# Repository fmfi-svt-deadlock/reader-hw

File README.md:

# PROJECT MOVED

This repository is now hosted here: https://gitlab.com/project-deadlock/reader/rdr-hw-fluocerite-model0

# reader-hw
Schematic, PCB layout and box for the Reader

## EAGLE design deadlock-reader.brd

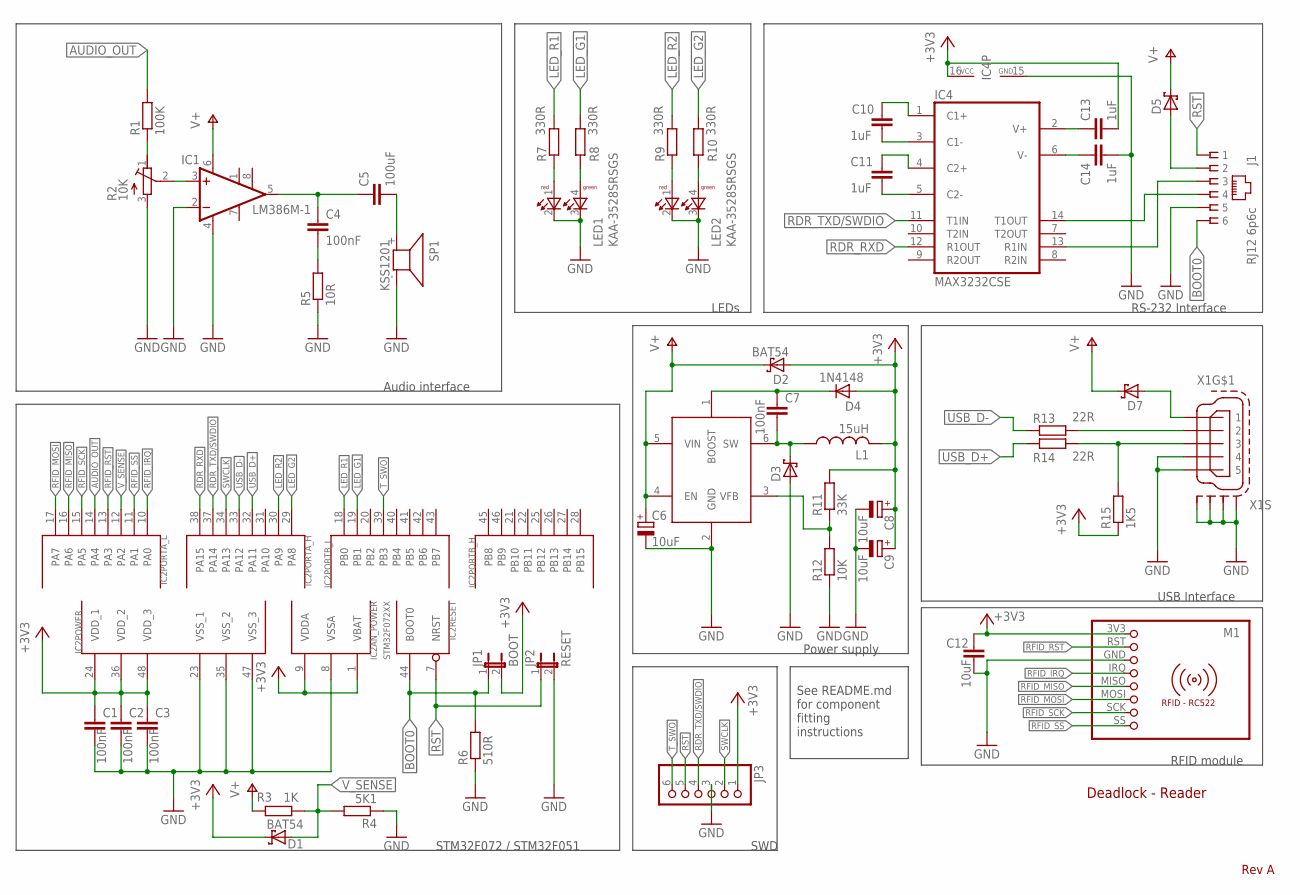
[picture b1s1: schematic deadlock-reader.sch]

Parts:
C1, C2, C3, C4, C7: 100nF; C0805
C5: 100uF; C1206
C6: 10uF; SMC_D
C8, C9: 10uF; A/3216-18R
C10, C11, C13, C14: 1uF; C0805
C12: 10uF; C0805
D1, D2: BAT54; SOT23
D3, D5, D7: BAT60J; SOD323_ST
D4: 1N4148; SOD323-W
IC1: LM386M-1; SO08
IC2: STM32F072XX; TQFP48
IC3: MCP16301/H; SOT23-6
IC4: MAX3232CSE; SO16
J1: RJ12 6p6c; RJ11-NO_SHIELD
JP1: BOOT; JP1
JP2: RESET; JP1
JP3: PINHD-1X6; 1X06
L1: 15uH; PIS2816
LED1, LED2: KAA-3528SRSGS
M1: RFID-RC522
R1: 100K; M0805
R2: 10K; RTRIM3314G
R3: 1K; R0805
R4: 5K1; R0805
R5: 10R; R0805
R6: 510R; R0805
R7, R8, R9, R10: 330R; R0805
R11: 33K; R0805
R12: 10K; R0805
R13, R14: 22R; R0805
R15: 1K5; R0805
SP1: KSS1201
X1: MINI-USB-SCHIELD-32005-301; 32005-301

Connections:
+3V3: C1.1, C2.1, C3.1, C8.+, C9.+, C12.1, C13.2, D1.3 (C), D2.1 (A), D4.A, IC2.1 (VBAT), IC2.9 (VDDA), IC2.24 (VDD_1), IC2.36 (VDD_2), IC2.48 (VDD_3), IC4.16 (VCC), JP1.2, JP3.1, L1.2, M1.3V3 (1), R11.2, R15.1
AUDIO_OUT: IC2.14 (PA4), R1.2
BOOT0: IC2.44 (BOOT0), J1.6, JP1.1, R6.2
GND: C1.2, C2.2, C3.2, C6.-, C8.-, C9.-, C12.2, C14.2, D3.A, IC1.2 (-IN), IC1.4 (GND), IC2.8 (VSSA), IC2.23 (VSS_1), IC2.35 (VSS_2), IC2.47 (VSS_3), IC3.2 (GND), IC4.15 (GND), J1.5, JP2.2, JP3.3, LED1.2 (C-RED), LED1.3 (C-GREEN), LED2.2 (C-RED), LED2.3 (C-GREEN), M1.GND (3), R2.3 (A), R4.1, R5.1, R6.1, R12.1, SP1.- (2), X1.4, X1.5, X1.M1 (S1), X1.M2 (S2), X1.M3 (S3), X1.M4 (S4)
LED_G1: IC2.19 (PB1), R8.2
LED_G2: IC2.29 (PA8), R10.2
LED_R1: IC2.18 (PB0), R7.2
LED_R2: IC2.30 (PA9), R9.2
unnamed: IC4.13 (R1IN), J1.3
unnamed: IC4.14 (T1OUT), J1.4
unnamed: C10.1, IC4.1 (C1+)
unnamed: C10.2, IC4.3 (C1-)
unnamed: C11.1, IC4.4 (C2+)
unnamed: C11.2, IC4.5 (C2-)
unnamed: C13.1, IC4.2 (V+)
unnamed: C14.1, IC4.6 (V-)
unnamed: D5.A, J1.2
unnamed: LED2.1 (A-RED), R9.1
unnamed: D7.A, X1.1
unnamed: R13.2, X1.2
unnamed: R14.2, R15.2, X1.3
unnamed: R1.1, R2.1 (E)
unnamed: IC1.3 (+IN), R2.2 (S)
unnamed: C4.1, C5.1, IC1.5 (OUT)
unnamed: C4.2, R5.2
unnamed: C5.2, SP1.+ (1)
unnamed: LED1.1 (A-RED), R7.1
unnamed: LED1.4 (A-GREEN), R8.1
unnamed: LED2.4 (A-GREEN), R10.1
unnamed: C7.2, D3.C, IC3.6 (SW), L1.1
unnamed: C7.1, D4.C, IC3.1 (BOOST)
unnamed: IC3.3 (VFB), R11.1, R12.2
RDR_RXD: IC2.38 (PA15), IC4.12 (R1OUT)
RDR_TXD/SWDIO: IC2.37 (PA14), IC4.11 (T1IN), JP3.4
RFID_IRQ: IC2.10 (PA0), M1.IRQ (4)
RFID_MISO: IC2.16 (PA6), M1.MISO (5)
RFID_MOSI: IC2.17 (PA7), M1.MOSI (6)
RFID_RST: IC2.13 (PA3), M1.RST (2)
RFID_SCK: IC2.15 (PA5), M1.SCK (7)
RFID_SS: IC2.11 (PA1), M1.SS (8)
RST: IC2.7 (NRST), J1.1, JP2.1, JP3.5
SWCLK: IC2.34 (PA13), JP3.2
T_SWO: IC2.39 (PB3), JP3.6
USB_D+: IC2.32 (PA11), R14.1
USB_D-: IC2.33 (PA12), R13.1
V+: C6.+, D2.3 (C), D5.C, D7.C, IC1.6 (VS), IC3.4 (EN), IC3.5 (VIN), R3.2
V_SENSE: D1.1 (A), IC2.12 (PA2), R3.1, R4.2

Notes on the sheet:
Deadlock - Reader
Rev A
RS-232 Interface
USB Interface
Audio interface
LEDs
STM32F072 / STM32F051
RFID module
SWD
Power supply
See README.md for component fitting instructions

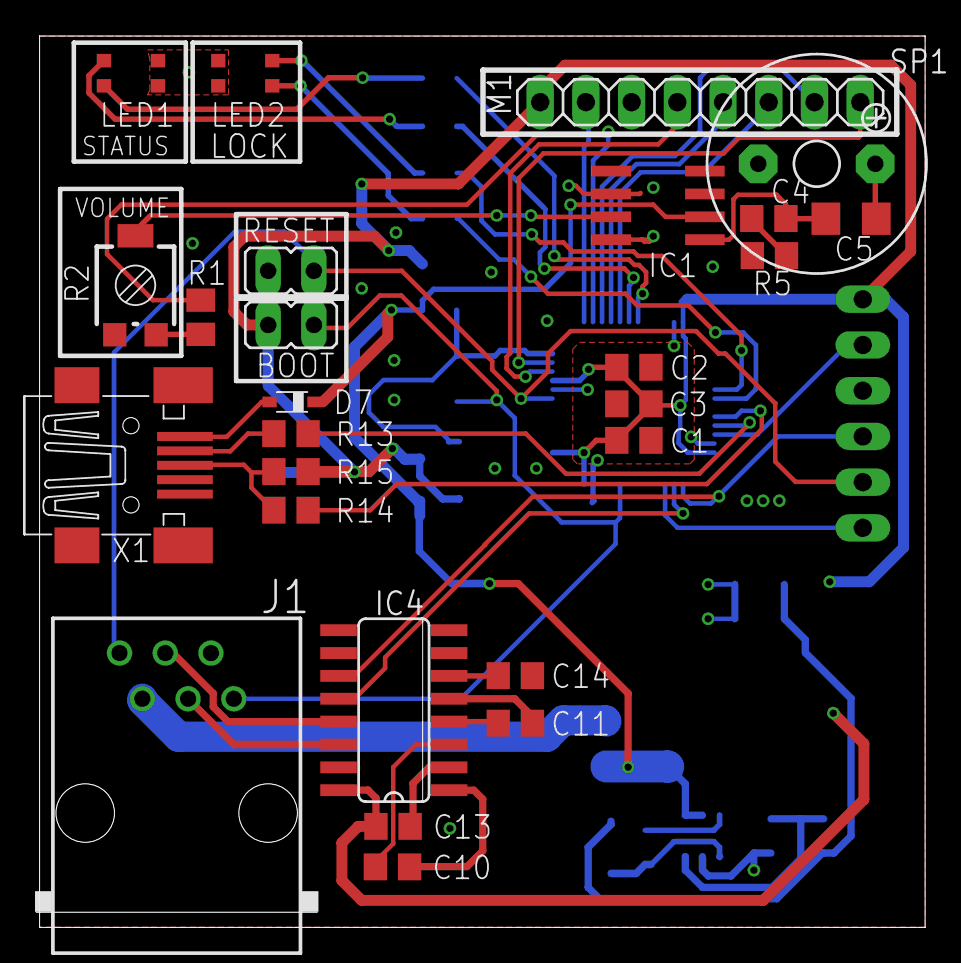
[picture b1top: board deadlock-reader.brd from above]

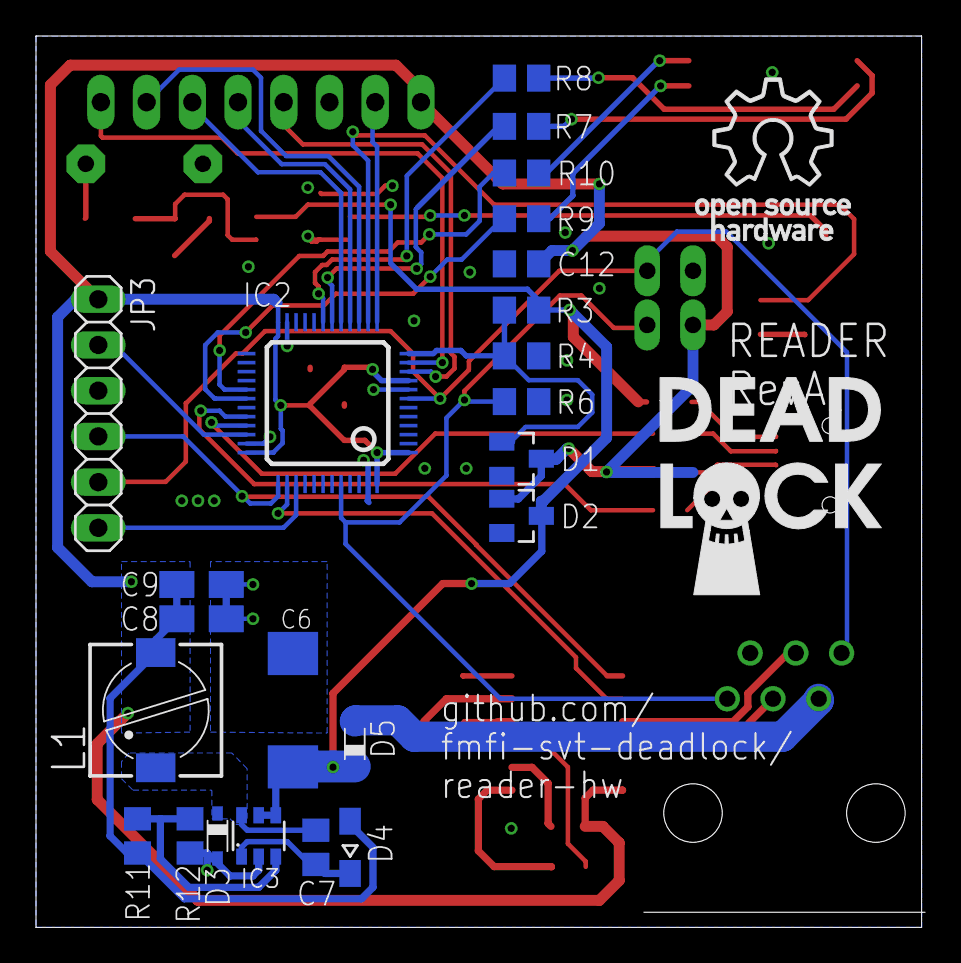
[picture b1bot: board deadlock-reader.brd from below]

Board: 2 copper layers, 49.4 x 49.5 mm, 49 parts (23 on the bottom side), 47 nets.

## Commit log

2015-03-19 Create a new project
2015-03-19 Add empty schematic
2015-03-27 Add RS-232 interface
2015-03-27 Add audio output
2015-03-29 Minor mid-review fixes
2015-03-29 Add LEDs
2015-03-29 Add volume resistor ladder for audio output
2015-03-29 Add STM32F0[72|51] MCU
2015-03-29 Add RFID module
2015-03-29 Add SWD header
2015-03-30 Add power supply
2015-03-30 Finishing touches for revA
2015-03-30 Minor value tweaks
2015-03-30 Review-induced fixes
2015-07-05 Rename project to Deadlock
2015-07-05 Remove all occurences of name 'Gate'
2015-07-21 User trimmer to regulate audio volume instead of digital pot
2015-07-25 Select components from distributor and adjust footprints
2015-08-06 Draft component placements
2015-08-06 Optimize component placements
2015-10-21 Final component placement
2015-10-21 [WIP] Route the power converter
2015-10-21 [WIP] Fix DRC errors on power converter layout
2015-10-21 [WIP] Route debug and RFID connectors to the MCU
2015-10-21 [WIP] Route leds and audio interface
2015-10-21 [WIP] Route RS-232 and USB interfaces
2015-10-22 [WIP] Route misc remaining signal lines
2015-10-22 [WIP] Route power distribution network
2015-10-22 Create ground planes, board routing finished
2015-10-23 Incorporate revA board review fixes
2015-10-23 Reorganize component labels on the silkscreen
2015-10-23 Add logos to the silkscreen
2015-10-26 Fix silkscreen logos; now they are exportable
2015-10-26 Enlarge repo address on silkscreen
2015-10-26 Add exported gerber files for revA
2015-10-31 Update LICENSE - project renamed from gate
2016-01-12 Bump copyright year
2016-05-27 add plexiglass reader box
2016-11-17 Add documentation stub
2017-01-12 new version of plexiglass box
